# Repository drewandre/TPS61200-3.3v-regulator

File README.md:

# TPS61200 3.3v regulator with Soft Power Switch

Low-noise TPS61200 3.3v regulator with soft power circuitry.

When user depresses momentary switch, p-mosfet channel is opened and pin 6 of the TPS61200 (EN / enable pin) is pulled HIGH. This turns the regulator on and supplies a steady, low-noise 3.3v output. ***Important:*** Microcontroller needs to write a digital HIGH to the KILL pin upon startup to keep channel open and regulator turned on.

To turn, MCU should write a digital LOW to the KILL pin. This closes the p-channel mosefet and turns off regulator.

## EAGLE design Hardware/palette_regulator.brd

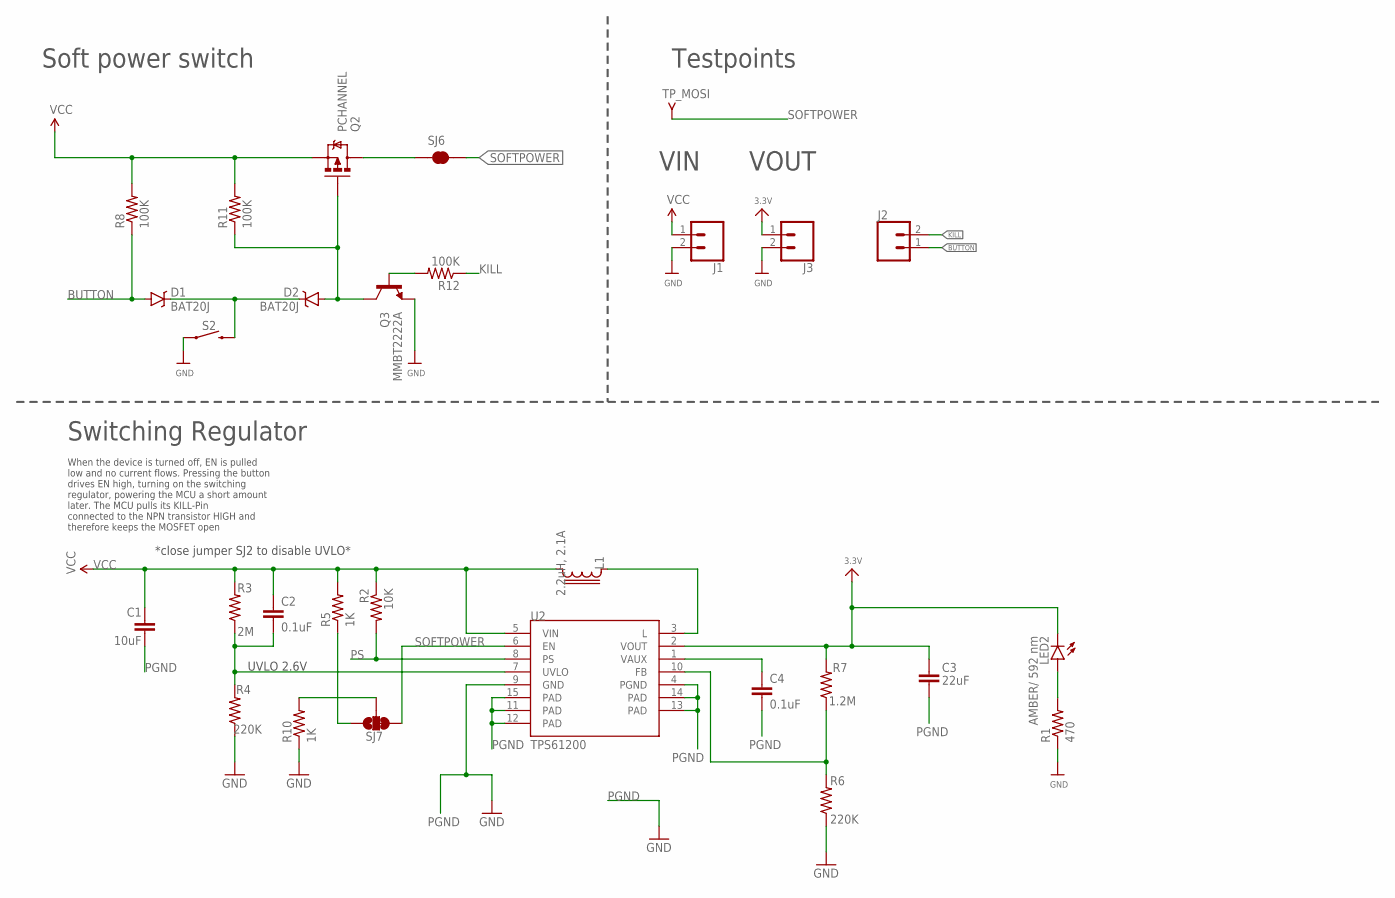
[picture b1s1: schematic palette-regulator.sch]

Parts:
C1: 10uF; 0603-CAP
C2, C4: 0.1uF; 0603-CAP
C3: 22uF; 0603-CAP
D1, D2: BAT20J; SOD-323
J1, J2, J3: CONN_02; 1X02
L1: 2.2uH, 2.1A; LPS3015
LED2: AMBER/ 592 nm; LED-0603
Q2: PCHANNEL; SOT23-3; MPN BSS84LT1G
Q3: MMBT2222A; SOT23-3
R1: 470; 0603-RES
R2: 10K; 0603-RES
R3: 2M; 0603-RES
R4, R6: 220K; 0603-RES
R5, R10: 1K; 0603-RES
R7: 1.2M; 0603-RES
R8, R11, R12: 100K; 0603-RES
S2: MOMENTARY-SWITCH-SPST-PTH-6.0MM; TACTILE_SWITCH_PTH_6.0MM; MPN PTS645SH50SMTR 92 LFS
SJ6: JUMPER-PAD-2-NC_BY_TRACE; PAD-JUMPER-2-NC_BY_TRACE_YES_SILK
SJ7: JUMPER-PAD-3-2OF3_NC_BY_TRACE; PAD-JUMPER-3-2OF3_NC_BY_TRACE_YES_SILK_FULL_BOX
TP_MOSI: MOSI; PAD-016
U2: TPS61200; QFN-10_PAD

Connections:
3.3V: C3.1, J3.1, LED2.C, R7.2, U2.2 (VOUT)
BUTTON: D1.A, J2.1, R8.1
FB: R6.2, R7.1, U2.10 (FB)
GND: J1.2, J3.2, Q3.2 (E), R1.1, R4.1, R6.1, R10.1, S2.1
KILL: J2.2, R12.1
unnamed: R10.2, SJ7.2
unnamed: L1.1, U2.3 (L)
unnamed: D2.A, Q2.1 (G), Q3.3 (C), R11.1
unnamed: Q3.1 (B), R12.2
unnamed: R5.1, SJ7.1
unnamed: D1.C, D2.C, S2.3 (2)
unnamed: Q2.3 (D), SJ6.1
unnamed: LED2.A, R1.2
PGND: C1.2, C3.2, C4.2, U2.4 (PGND), U2.9 (GND), U2.11 (PAD), U2.12 (PAD), U2.13 (PAD), U2.14 (PAD), U2.15 (PAD)
PS: R2.2, U2.8 (PS)
SOFTPOWER: SJ6.2, SJ7.3, TP_MOSI.1, U2.6 (EN)
UVLO: C2.2, R3.1, R4.2, U2.7 (UVLO)
VAUX: C4.1, U2.1 (VAUX)
VCC: C1.1, C2.1, J1.1, L1.2, Q2.2 (S), R2.1, R3.2, R5.2, R8.2, R11.2, U2.5 (VIN)

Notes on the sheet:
UVLO 2.6V
*close jumper SJ2 to disable UVLO*
Switching Regulator
When the device is turned off, EN is pulled low and no current flows. Pressing the button drives EN high, turning on the switching regulator, powering the MCU a short amount later. The MCU pulls its KILL-Pin connected to the NPN transistor HIGH and therefore keeps the MOSFET open
Soft power switch
Testpoints
VIN
VOUT

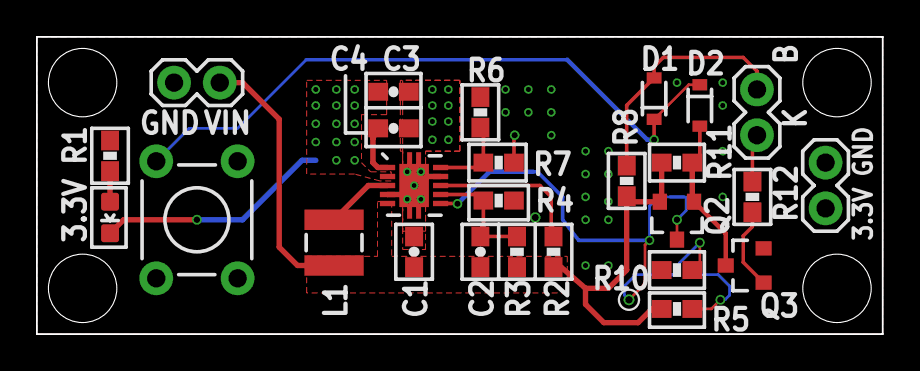
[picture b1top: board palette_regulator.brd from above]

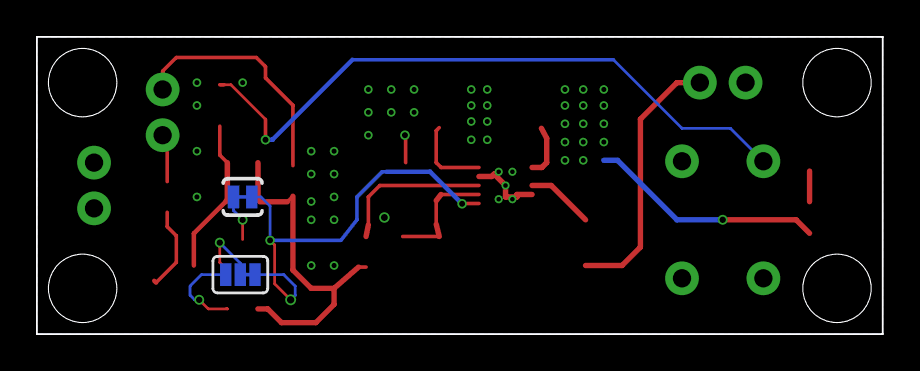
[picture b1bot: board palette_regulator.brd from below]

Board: 4 copper layers, 47.0 x 16.5 mm, 29 parts (2 on the bottom side), 19 nets.

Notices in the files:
parts and their libraries:
SparkFun-DiscreteSemi: Licensing: Creative Commons ShareAlike 4.0 International - https://creativecommons.org/licenses/by-sa/4.0
